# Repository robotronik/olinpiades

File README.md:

# Git pour les yeux du char des ol'INPiade

## Installation du dépot :
Pour cloner ce dépot:
```
git clone --recurse-submodules git@github.com:robotronik/olinpiades.git
```
## pré-requis : 
 
### Programmation
- arm-none-eabi-gcc: pour compiler le programme du stm32 ainsi que ces librairies (arm-none-eabi-**** sur arch linux)
- openocd: pour envoyer le programme au stm32
- meson pour compiler
### Génération des images
- Python
### Carte élctronique : 
- kicad 5

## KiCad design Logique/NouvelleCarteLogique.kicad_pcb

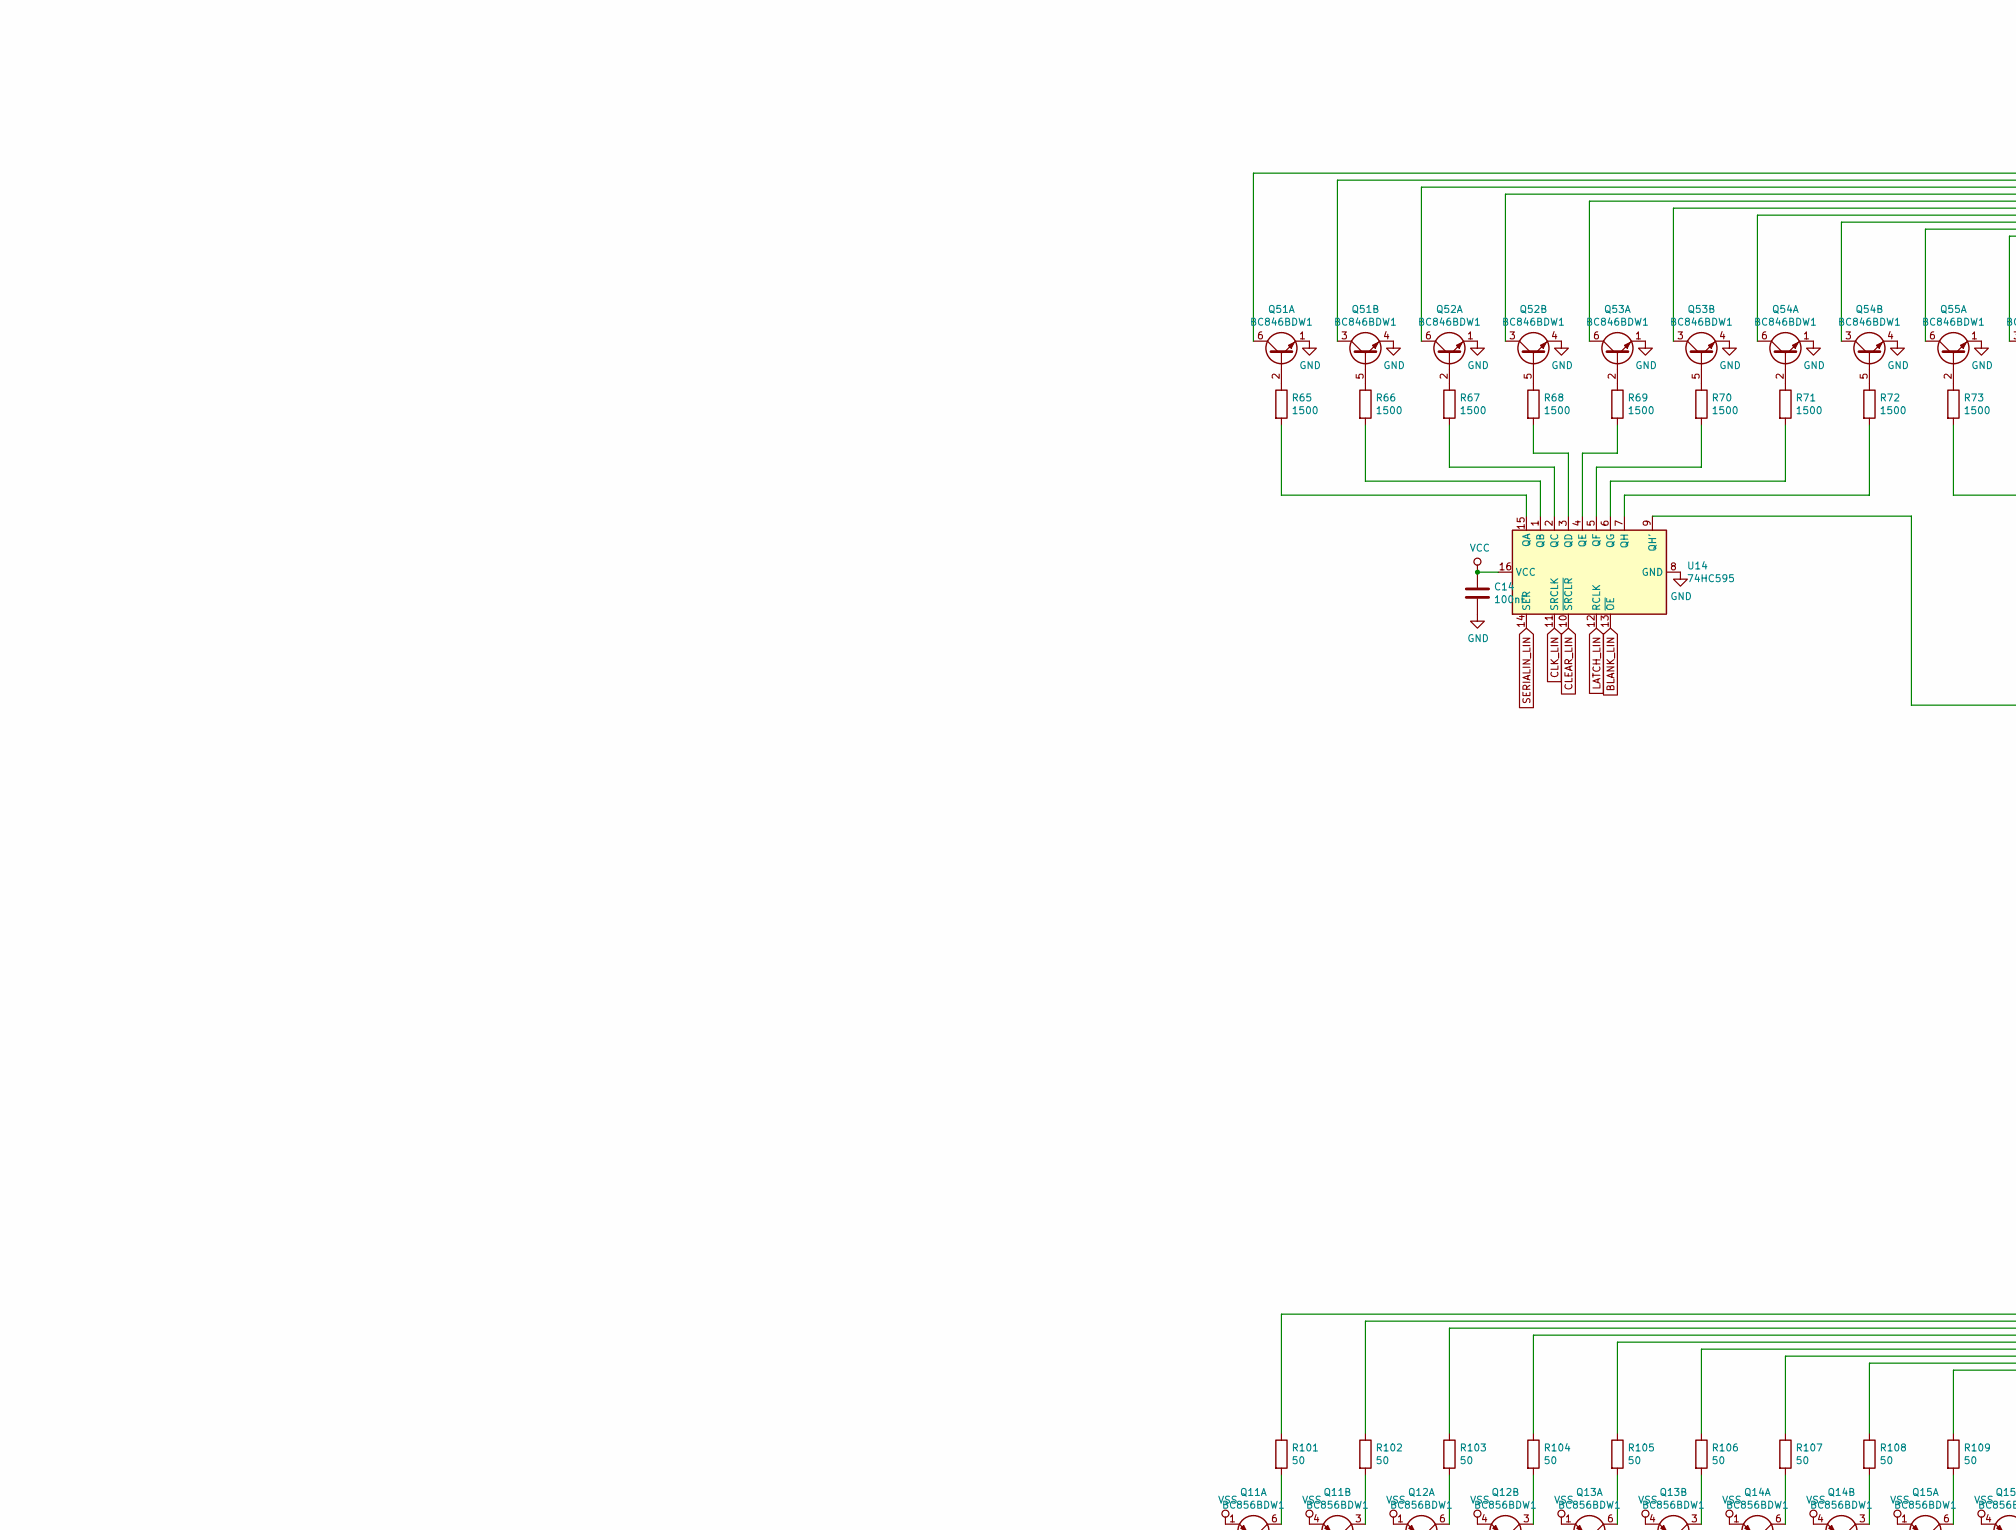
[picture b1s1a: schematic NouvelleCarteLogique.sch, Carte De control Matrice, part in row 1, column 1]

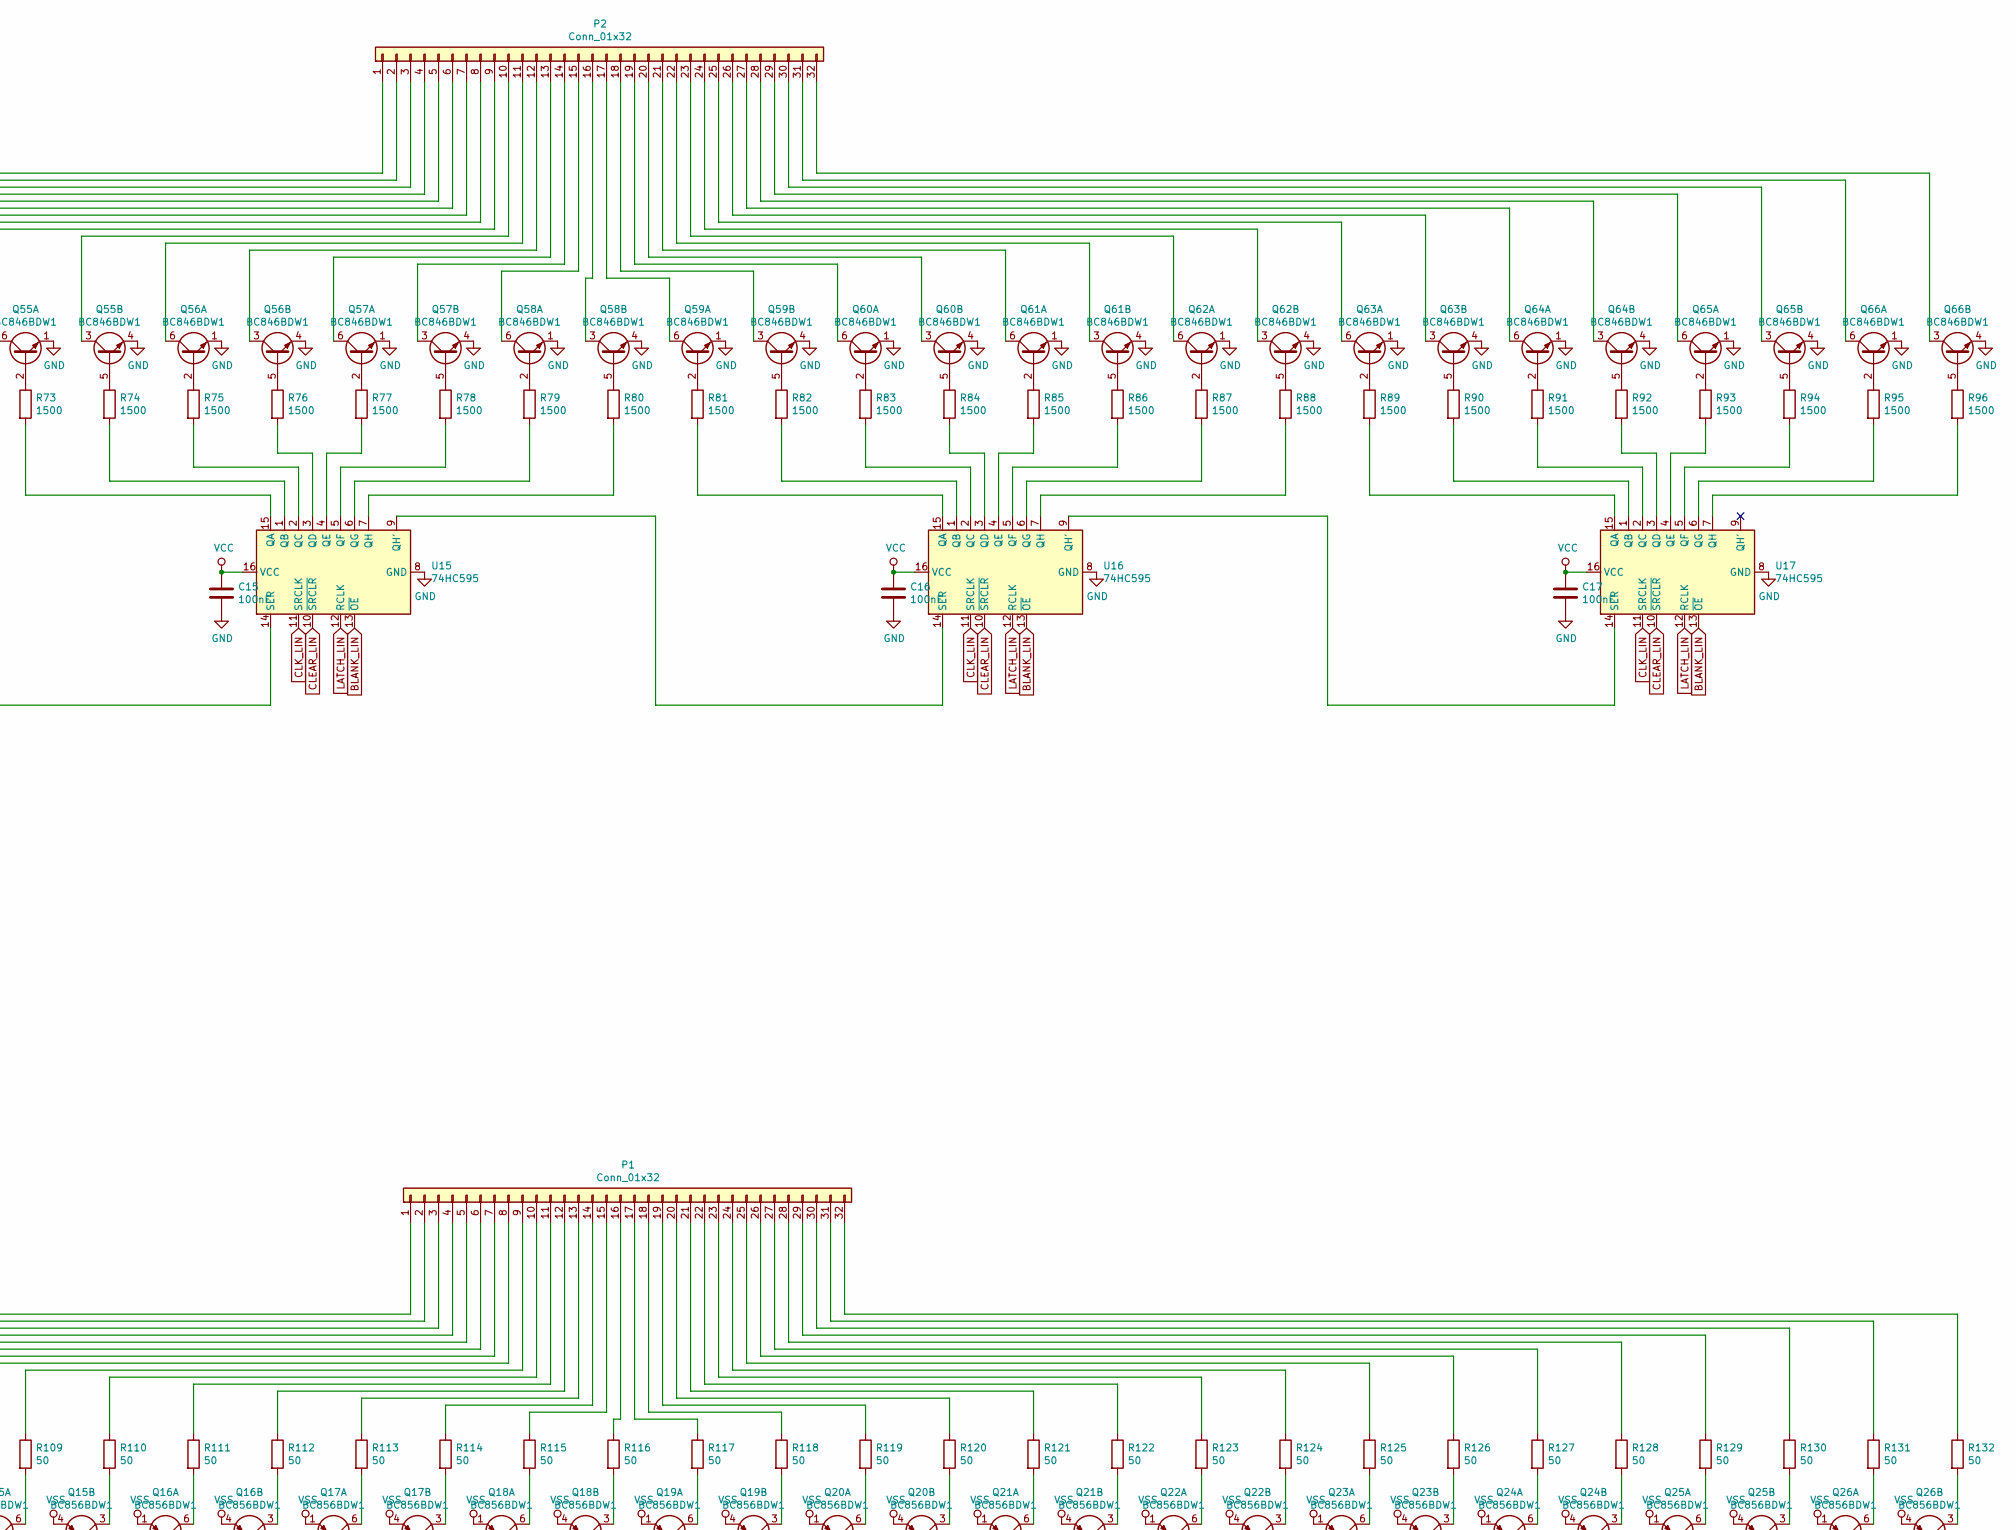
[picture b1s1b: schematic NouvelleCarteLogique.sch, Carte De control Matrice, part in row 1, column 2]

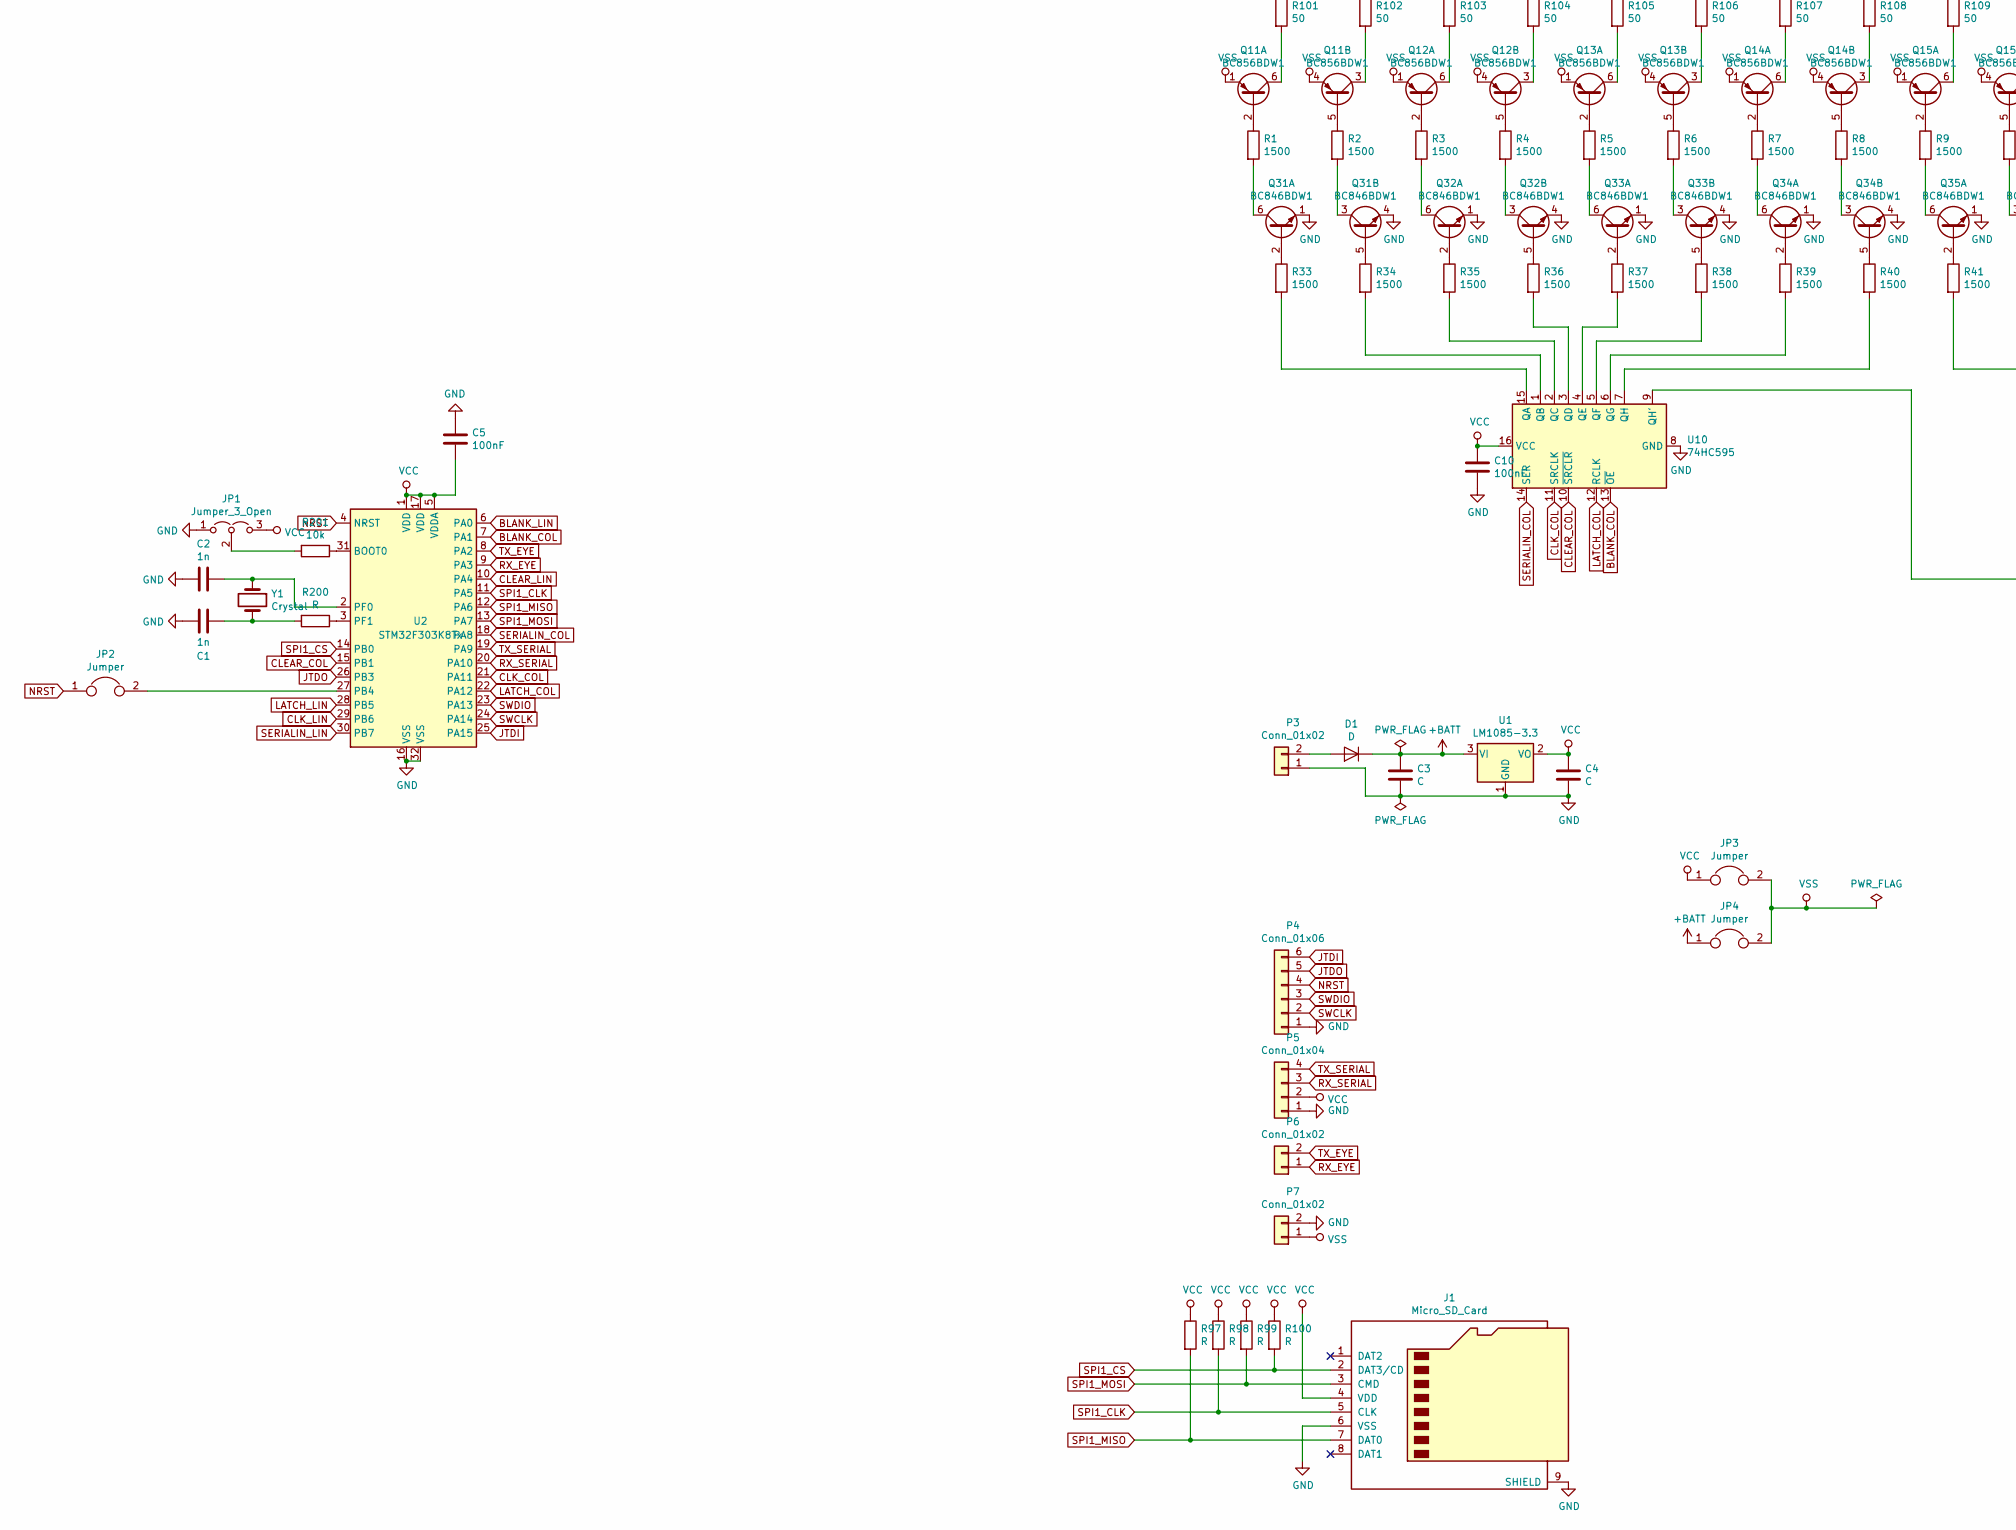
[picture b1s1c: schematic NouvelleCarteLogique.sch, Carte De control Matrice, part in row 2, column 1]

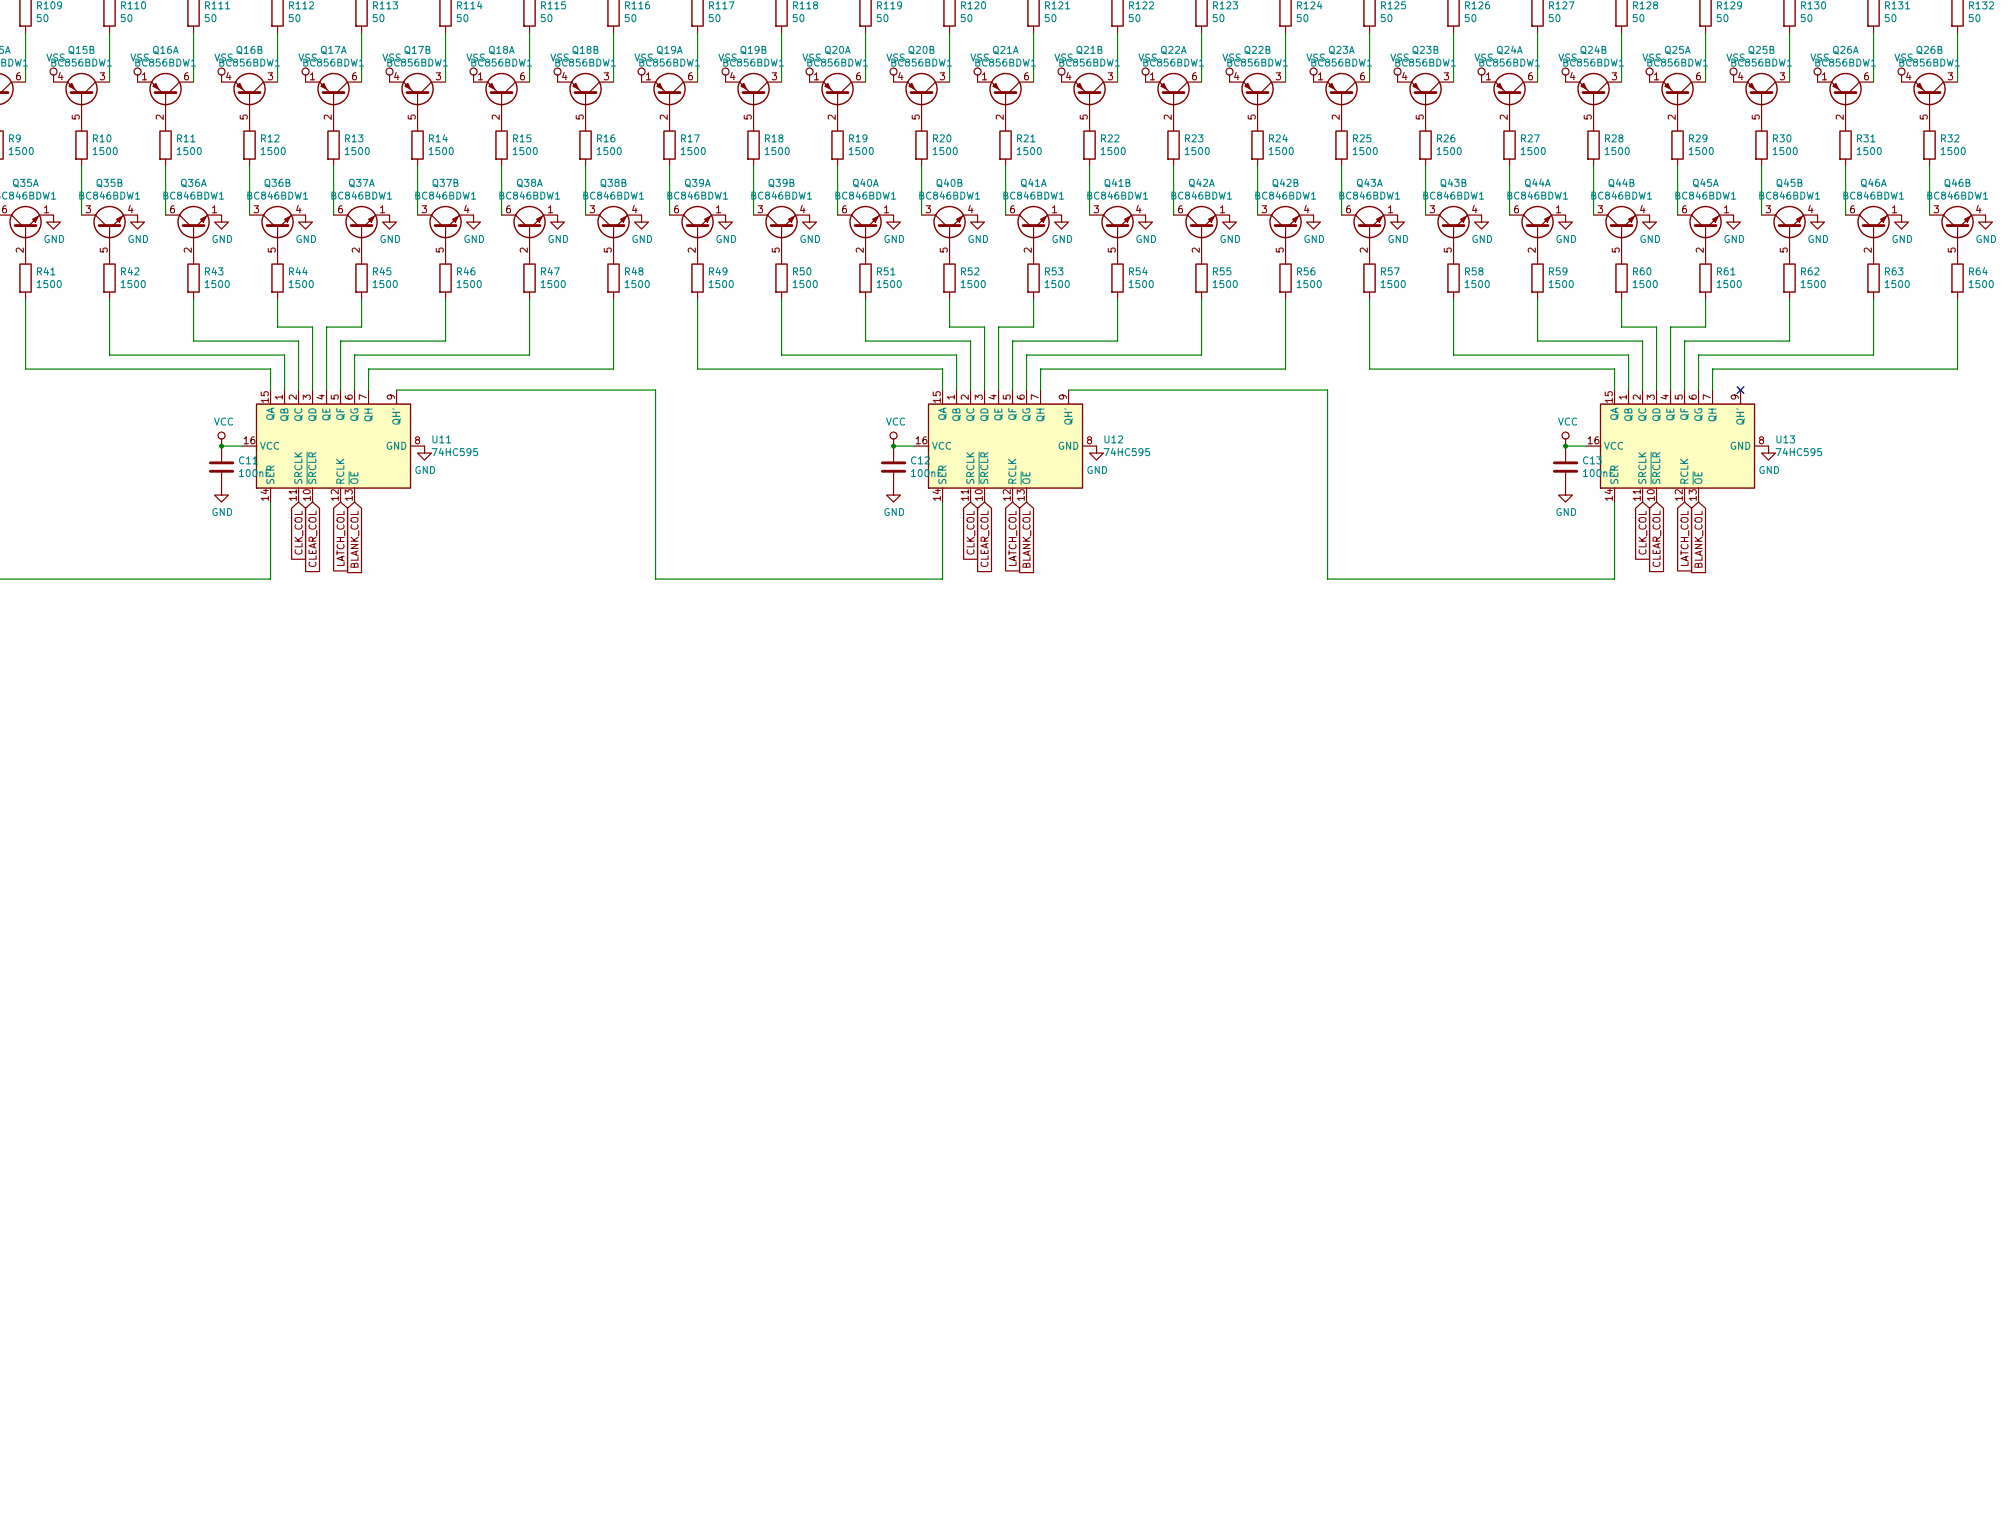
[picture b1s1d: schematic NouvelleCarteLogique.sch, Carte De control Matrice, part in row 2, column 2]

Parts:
C1, C2: 1n; C_0805_2012Metric_Pad1.15x1.40mm_HandSolder
C3, C4: C; C_0805_2012Metric_Pad1.15x1.40mm_HandSolder
C5, C10, C11, C12, C13, C14, C15, C16, C17: 100nF; C_0805_2012Metric_Pad1.15x1.40mm_HandSolder
D1: D; D_SMA_Handsoldering
J1: Micro_SD_Card; microSD_HC_Wuerth_693072010801
JP1: Jumper_3_Open; PinHeader_1x03_P2.54mm_Vertical
JP2, JP3, JP4: Jumper; R_0805_2012Metric_Pad1.15x1.40mm_HandSolder
P1, P2: Conn_01x32; PinHeader_1x32_P2.54mm_Vertical
P3, P6, P7: Conn_01x02; TerminalBlock_bornier-2_P5.08mm
P4: Conn_01x06; PinHeader_1x06_P2.54mm_Horizontal
P5: Conn_01x04; PinHeader_1x04_P2.54mm_Horizontal
Q11, Q12, Q13, Q14, Q15, Q16, Q17, Q18, Q19, Q20, Q21, Q22, Q23, Q24, Q25, Q26: BC856BDW1; SOT-363_SC-70-6
Q31, Q32, Q33, Q34, Q35, Q36, Q37, Q38, Q39, Q40, Q41, Q42, Q43, Q44, Q45, Q46, Q51, Q52, Q53, Q54, Q55, Q56, Q57, Q58, Q59, Q60, Q61, Q62, Q63, Q64, Q65, Q66: BC846BDW1; SOT-363_SC-70-6
R1, R2, R3, R4, R5, R6, R7, R8, R9, R10, R11, R12, R13, R14, R15, R16, R17, R18, R19, R20, R21, R22, R23, R24, R25, R26, R27, R28, R29, R30, R31, R32, R33, R34, R35, R36, R37, R38, R39, R40, R41, R42, R43, R44, R45, R46, R47, R48, R49, R50, R51, R52, R53, R54, R55, R56, R57, R58, R59, R60, R61, R62, R63, R64, R65, R66, R67, R68, R69, R70, R71, R72, R73, R74, R75, R76, R77, R78, R79, R80, R81, R82, R83, R84, R85, R86, R87, R88, R89, R90, R91, R92, R93, R94, R95, R96: 1500; R_0805_2012Metric_Pad1.15x1.40mm_HandSolder
R97, R98, R99, R100, R200: R; R_0805_2012Metric_Pad1.15x1.40mm_HandSolder
R101, R102, R103, R104, R105, R106, R107, R108, R109, R110, R111, R112, R113, R114, R115, R116, R117, R118, R119, R120, R121, R122, R123, R124, R125, R126, R127, R128, R129, R130, R131, R132: 50; R_0805_2012Metric_Pad1.15x1.40mm_HandSolder
R201: 10k; R_0805_2012Metric_Pad1.15x1.40mm_HandSolder
U1: LM1085-3.3; TO-263-3_TabPin2
U2: STM32F303K8Tx; LQFP-32_7x7mm_P0.8mm
U10, U11, U12, U13, U14, U15, U16, U17: 74HC595; TSSOP-16_4.4x5mm_P0.65mm
Y1: Crystal; Crystal_HC49-4H_Vertical

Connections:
+BATT: C3.1, D1.1 (K), JP4.1, U1.3 (VI)
BLANK_COL: U2.7 (PA1), U10.13 (~OE), U11.13 (~OE), U12.13 (~OE), U13.13 (~OE)
BLANK_LIN: U2.6 (PA0), U14.13 (~OE), U15.13 (~OE), U16.13 (~OE), U17.13 (~OE)
CLEAR_COL: U2.15 (PB1), U10.10 (~SRCLR), U11.10 (~SRCLR), U12.10 (~SRCLR), U13.10 (~SRCLR)
CLEAR_LIN: U2.10 (PA4), U14.10 (~SRCLR), U15.10 (~SRCLR), U16.10 (~SRCLR), U17.10 (~SRCLR)
CLK_COL: U2.21 (PA11), U10.11 (SRCLK), U11.11 (SRCLK), U12.11 (SRCLK), U13.11 (SRCLK)
CLK_LIN: U2.29 (PB6), U14.11 (SRCLK), U15.11 (SRCLK), U16.11 (SRCLK), U17.11 (SRCLK)
GND: C1.2, C2.2, C3.2, C4.2, C5.1, C10.2, C11.2, C12.2, C13.2, C14.2, C15.2, C16.2, C17.2, J1.6 (VSS), J1.9 (SHIELD), JP1.1 (A), P3.1, P4.1, P5.1, P7.2, Q31.1 (E1), Q31.4 (E2), Q32.1 (E1), Q32.4 (E2), Q33.1 (E1), Q33.4 (E2), Q34.1 (E1), Q34.4 (E2), Q35.1 (E1), Q35.4 (E2), Q36.1 (E1), Q36.4 (E2), Q37.1 (E1), Q37.4 (E2), Q38.1 (E1), Q38.4 (E2), Q39.1 (E1), Q39.4 (E2), Q40.1 (E1), Q40.4 (E2), Q41.1 (E1), Q41.4 (E2), Q42.1 (E1), Q42.4 (E2), Q43.1 (E1), Q43.4 (E2), Q44.1 (E1), Q44.4 (E2), Q45.1 (E1), Q45.4 (E2), Q46.1 (E1), Q46.4 (E2), Q51.1 (E1), Q51.4 (E2), Q52.1 (E1), Q52.4 (E2), Q53.1 (E1), Q53.4 (E2), Q54.1 (E1), Q54.4 (E2), Q55.1 (E1), Q55.4 (E2), Q56.1 (E1), Q56.4 (E2), Q57.1 (E1), Q57.4 (E2), Q58.1 (E1), Q58.4 (E2), Q59.1 (E1), Q59.4 (E2), Q60.1 (E1), Q60.4 (E2), Q61.1 (E1), Q61.4 (E2), Q62.1 (E1), Q62.4 (E2), Q63.1 (E1), Q63.4 (E2), Q64.1 (E1), Q64.4 (E2), Q65.1 (E1), Q65.4 (E2), Q66.1 (E1), Q66.4 (E2), U1.1 (GND), U2.16 (VSS), U2.32 (VSS), U10.8 (GND), U11.8 (GND), U12.8 (GND), U13.8 (GND), U14.8 (GND), U15.8 (GND), U16.8 (GND), U17.8 (GND)
JTDI: P4.6, U2.25 (PA15)
JTDO: P4.5, U2.26 (PB3)
LATCH_COL: U2.22 (PA12), U10.12 (RCLK), U11.12 (RCLK), U12.12 (RCLK), U13.12 (RCLK)
LATCH_LIN: U2.28 (PB5), U14.12 (RCLK), U15.12 (RCLK), U16.12 (RCLK), U17.12 (RCLK)
NRST: JP2.1, P4.4, U2.4 (NRST)
unnamed: C1.1, R200.2, Y1.2
unnamed: C2.1, U2.2 (PF0), Y1.1
unnamed: D1.2 (A), P3.2
unnamed: JP1.2 (C), R201.2
unnamed: JP2.2, U2.27 (PB4)
unnamed: P1.1, R101.1
unnamed: P1.2, R102.1
unnamed: P1.3, R103.1
unnamed: P1.4, R104.1
unnamed: P1.5, R105.1
unnamed: P1.6, R106.1
unnamed: P1.7, R107.1
unnamed: P1.8, R108.1
unnamed: P1.9, R109.1
unnamed: P1.10, R110.1
unnamed: P1.11, R111.1
unnamed: P1.12, R112.1
unnamed: P1.13, R113.1
unnamed: P1.14, R114.1
unnamed: P1.15, R115.1
unnamed: P1.16, R116.1
unnamed: P1.17, R117.1
unnamed: P1.18, R118.1
unnamed: P1.19, R119.1
unnamed: P1.20, R120.1
unnamed: P1.21, R121.1
unnamed: P1.22, R122.1
unnamed: P1.23, R123.1
unnamed: P1.24, R124.1
unnamed: P1.25, R125.1
unnamed: P1.26, R126.1
unnamed: P1.27, R127.1
unnamed: P1.28, R128.1
unnamed: P1.29, R129.1
unnamed: P1.30, R130.1
unnamed: P1.31, R131.1
unnamed: P1.32, R132.1
unnamed: P2.1, Q51.6 (C1)
unnamed: P2.2, Q51.3 (C2)
unnamed: P2.3, Q52.6 (C1)
unnamed: P2.4, Q52.3 (C2)
unnamed: P2.5, Q53.6 (C1)
unnamed: P2.6, Q53.3 (C2)
unnamed: P2.7, Q54.6 (C1)
unnamed: P2.8, Q54.3 (C2)
unnamed: P2.9, Q55.6 (C1)
unnamed: P2.10, Q55.3 (C2)
unnamed: P2.11, Q56.6 (C1)
unnamed: P2.12, Q56.3 (C2)
unnamed: P2.13, Q57.6 (C1)
unnamed: P2.14, Q57.3 (C2)
unnamed: P2.15, Q58.6 (C1)
unnamed: P2.16, Q58.3 (C2)
unnamed: P2.17, Q59.6 (C1)
unnamed: P2.18, Q59.3 (C2)
unnamed: P2.19, Q60.6 (C1)
unnamed: P2.20, Q60.3 (C2)
unnamed: P2.21, Q61.6 (C1)
unnamed: P2.22, Q61.3 (C2)
unnamed: P2.23, Q62.6 (C1)
unnamed: P2.24, Q62.3 (C2)
unnamed: P2.25, Q63.6 (C1)
unnamed: P2.26, Q63.3 (C2)
unnamed: P2.27, Q64.6 (C1)
unnamed: P2.28, Q64.3 (C2)
unnamed: P2.29, Q65.6 (C1)
unnamed: P2.30, Q65.3 (C2)
unnamed: P2.31, Q66.6 (C1)
unnamed: P2.32, Q66.3 (C2)
unnamed: Q11.2 (B1), R1.1
unnamed: Q11.3 (C2), R102.2
unnamed: Q11.5 (B2), R2.1
unnamed: Q11.6 (C1), R101.2
unnamed: Q12.2 (B1), R3.1
unnamed: Q12.3 (C2), R104.2
unnamed: Q12.5 (B2), R4.1
unnamed: Q12.6 (C1), R103.2
unnamed: Q13.2 (B1), R5.1
unnamed: Q13.3 (C2), R106.2
unnamed: Q13.5 (B2), R6.1
unnamed: Q13.6 (C1), R105.2
unnamed: Q14.2 (B1), R7.1
unnamed: Q14.3 (C2), R108.2
unnamed: Q14.5 (B2), R8.1
unnamed: Q14.6 (C1), R107.2
unnamed: Q15.2 (B1), R9.1
unnamed: Q15.3 (C2), R110.2
unnamed: Q15.5 (B2), R10.1
unnamed: Q15.6 (C1), R109.2
unnamed: Q16.2 (B1), R11.1
unnamed: Q16.3 (C2), R112.2
unnamed: Q16.5 (B2), R12.1
unnamed: Q16.6 (C1), R111.2
unnamed: Q17.2 (B1), R13.1
unnamed: Q17.3 (C2), R114.2
unnamed: Q17.5 (B2), R14.1
unnamed: Q17.6 (C1), R113.2
unnamed: Q18.2 (B1), R15.1
unnamed: Q18.3 (C2), R116.2
unnamed: Q18.5 (B2), R16.1
unnamed: Q18.6 (C1), R115.2
unnamed: Q19.2 (B1), R17.1
unnamed: Q19.3 (C2), R118.2
unnamed: Q19.5 (B2), R18.1
unnamed: Q19.6 (C1), R117.2
unnamed: Q20.2 (B1), R19.1
unnamed: Q20.3 (C2), R120.2
unnamed: Q20.5 (B2), R20.1
unnamed: Q20.6 (C1), R119.2
unnamed: Q21.2 (B1), R21.1
unnamed: Q21.3 (C2), R122.2
unnamed: Q21.5 (B2), R22.1
unnamed: Q21.6 (C1), R121.2
unnamed: Q22.2 (B1), R23.1
unnamed: Q22.3 (C2), R124.2
unnamed: Q22.5 (B2), R24.1
unnamed: Q22.6 (C1), R123.2
unnamed: Q23.2 (B1), R25.1
unnamed: Q23.3 (C2), R126.2
unnamed: Q23.5 (B2), R26.1
unnamed: Q23.6 (C1), R125.2
unnamed: Q24.2 (B1), R27.1
unnamed: Q24.3 (C2), R128.2
unnamed: Q24.5 (B2), R28.1
unnamed: Q24.6 (C1), R127.2
unnamed: Q25.2 (B1), R29.1
unnamed: Q25.3 (C2), R130.2
unnamed: Q25.5 (B2), R30.1
unnamed: Q25.6 (C1), R129.2
unnamed: Q26.2 (B1), R31.1
unnamed: Q26.3 (C2), R132.2
unnamed: Q26.5 (B2), R32.1
unnamed: Q26.6 (C1), R131.2
unnamed: Q31.2 (B1), R33.1
unnamed: Q31.3 (C2), R2.2
unnamed: Q31.5 (B2), R34.1
unnamed: Q31.6 (C1), R1.2
unnamed: Q32.2 (B1), R35.1
unnamed: Q32.3 (C2), R4.2
unnamed: Q32.5 (B2), R36.1
unnamed: Q32.6 (C1), R3.2
unnamed: Q33.2 (B1), R37.1
unnamed: Q33.3 (C2), R6.2
unnamed: Q33.5 (B2), R38.1
unnamed: Q33.6 (C1), R5.2
unnamed: Q34.2 (B1), R39.1
unnamed: Q34.3 (C2), R8.2
unnamed: Q34.5 (B2), R40.1
unnamed: Q34.6 (C1), R7.2
unnamed: Q35.2 (B1), R41.1
unnamed: Q35.3 (C2), R10.2
unnamed: Q35.5 (B2), R42.1
unnamed: Q35.6 (C1), R9.2
unnamed: Q36.2 (B1), R43.1
unnamed: Q36.3 (C2), R12.2
unnamed: Q36.5 (B2), R44.1
unnamed: Q36.6 (C1), R11.2
unnamed: Q37.2 (B1), R45.1
unnamed: Q37.3 (C2), R14.2
unnamed: Q37.5 (B2), R46.1
unnamed: Q37.6 (C1), R13.2
unnamed: Q38.2 (B1), R47.1
unnamed: Q38.3 (C2), R16.2
unnamed: Q38.5 (B2), R48.1
unnamed: Q38.6 (C1), R15.2
unnamed: Q39.2 (B1), R49.1
unnamed: Q39.3 (C2), R18.2
unnamed: Q39.5 (B2), R50.1
unnamed: Q39.6 (C1), R17.2
unnamed: Q40.2 (B1), R51.1
unnamed: Q40.3 (C2), R20.2
unnamed: Q40.5 (B2), R52.1
unnamed: Q40.6 (C1), R19.2
unnamed: Q41.2 (B1), R53.1
unnamed: Q41.3 (C2), R22.2
unnamed: Q41.5 (B2), R54.1
unnamed: Q41.6 (C1), R21.2
unnamed: Q42.2 (B1), R55.1
unnamed: Q42.3 (C2), R24.2
unnamed: Q42.5 (B2), R56.1
unnamed: Q42.6 (C1), R23.2
unnamed: Q43.2 (B1), R57.1
unnamed: Q43.3 (C2), R26.2
unnamed: Q43.5 (B2), R58.1
unnamed: Q43.6 (C1), R25.2
unnamed: Q44.2 (B1), R59.1
unnamed: Q44.3 (C2), R28.2
unnamed: Q44.5 (B2), R60.1
unnamed: Q44.6 (C1), R27.2
unnamed: Q45.2 (B1), R61.1
unnamed: Q45.3 (C2), R30.2
unnamed: Q45.5 (B2), R62.1
unnamed: Q45.6 (C1), R29.2
unnamed: Q46.2 (B1), R63.1
unnamed: Q46.3 (C2), R32.2
unnamed: Q46.5 (B2), R64.1
unnamed: Q46.6 (C1), R31.2
unnamed: Q51.2 (B1), R65.1
unnamed: Q51.5 (B2), R66.1
unnamed: Q52.2 (B1), R67.1
unnamed: Q52.5 (B2), R68.1
unnamed: Q53.2 (B1), R69.1
unnamed: Q53.5 (B2), R70.1
unnamed: Q54.2 (B1), R71.1
unnamed: Q54.5 (B2), R72.1
unnamed: Q55.2 (B1), R73.1
unnamed: Q55.5 (B2), R74.1
unnamed: Q56.2 (B1), R75.1
unnamed: Q56.5 (B2), R76.1
unnamed: Q57.2 (B1), R77.1
unnamed: Q57.5 (B2), R78.1
unnamed: Q58.2 (B1), R79.1
unnamed: Q58.5 (B2), R80.1
unnamed: Q59.2 (B1), R81.1
unnamed: Q59.5 (B2), R82.1
unnamed: Q60.2 (B1), R83.1
unnamed: Q60.5 (B2), R84.1
unnamed: Q61.2 (B1), R85.1
unnamed: Q61.5 (B2), R86.1
unnamed: Q62.2 (B1), R87.1
unnamed: Q62.5 (B2), R88.1
unnamed: Q63.2 (B1), R89.1
unnamed: Q63.5 (B2), R90.1
unnamed: Q64.2 (B1), R91.1
unnamed: Q64.5 (B2), R92.1
unnamed: Q65.2 (B1), R93.1
unnamed: Q65.5 (B2), R94.1
unnamed: Q66.2 (B1), R95.1
unnamed: Q66.5 (B2), R96.1
unnamed: R33.2, U10.15 (QA)
unnamed: R34.2, U10.1 (QB)
unnamed: R35.2, U10.2 (QC)
unnamed: R36.2, U10.3 (QD)
unnamed: R37.2, U10.4 (QE)
unnamed: R38.2, U10.5 (QF)
unnamed: R39.2, U10.6 (QG)
unnamed: R40.2, U10.7 (QH)
unnamed: R41.2, U11.15 (QA)
unnamed: R42.2, U11.1 (QB)
unnamed: R43.2, U11.2 (QC)
unnamed: R44.2, U11.3 (QD)
unnamed: R45.2, U11.4 (QE)
unnamed: R46.2, U11.5 (QF)
unnamed: R47.2, U11.6 (QG)
unnamed: R48.2, U11.7 (QH)
unnamed: R49.2, U12.15 (QA)
unnamed: R50.2, U12.1 (QB)
unnamed: R51.2, U12.2 (QC)
unnamed: R52.2, U12.3 (QD)
unnamed: R53.2, U12.4 (QE)
unnamed: R54.2, U12.5 (QF)
unnamed: R55.2, U12.6 (QG)
unnamed: R56.2, U12.7 (QH)
unnamed: R57.2, U13.15 (QA)
unnamed: R58.2, U13.1 (QB)
unnamed: R59.2, U13.2 (QC)
unnamed: R60.2, U13.3 (QD)
unnamed: R61.2, U13.4 (QE)
unnamed: R62.2, U13.5 (QF)
unnamed: R63.2, U13.6 (QG)
unnamed: R64.2, U13.7 (QH)
unnamed: R65.2, U14.15 (QA)
unnamed: R66.2, U14.1 (QB)
unnamed: R67.2, U14.2 (QC)
unnamed: R68.2, U14.3 (QD)
unnamed: R69.2, U14.4 (QE)
unnamed: R70.2, U14.5 (QF)
unnamed: R71.2, U14.6 (QG)
unnamed: R72.2, U14.7 (QH)
unnamed: R73.2, U15.15 (QA)
unnamed: R74.2, U15.1 (QB)
unnamed: R75.2, U15.2 (QC)
unnamed: R76.2, U15.3 (QD)
unnamed: R77.2, U15.4 (QE)
unnamed: R78.2, U15.5 (QF)
unnamed: R79.2, U15.6 (QG)
unnamed: R80.2, U15.7 (QH)
unnamed: R81.2, U16.15 (QA)
unnamed: R82.2, U16.1 (QB)
unnamed: R83.2, U16.2 (QC)
unnamed: R84.2, U16.3 (QD)
unnamed: R85.2, U16.4 (QE)
unnamed: R86.2, U16.5 (QF)
unnamed: R87.2, U16.6 (QG)
unnamed: R88.2, U16.7 (QH)
unnamed: R89.2, U17.15 (QA)
unnamed: R90.2, U17.1 (QB)
unnamed: R91.2, U17.2 (QC)
unnamed: R92.2, U17.3 (QD)
unnamed: R93.2, U17.4 (QE)
unnamed: R94.2, U17.5 (QF)
unnamed: R95.2, U17.6 (QG)
unnamed: R96.2, U17.7 (QH)
unnamed: R200.1, U2.3 (PF1)
unnamed: R201.1, U2.31 (BOOT0)
unnamed: U10.9 (QH'), U11.14 (SER)
unnamed: U11.9 (QH'), U12.14 (SER)
unnamed: U12.9 (QH'), U13.14 (SER)
unnamed: U14.9 (QH'), U15.14 (SER)
unnamed: U15.9 (QH'), U16.14 (SER)
unnamed: U16.9 (QH'), U17.14 (SER)
RX_EYE: P6.1, U2.9 (PA3)
RX_SERIAL: P5.3, U2.20 (PA10)
SERIALIN_COL: U2.18 (PA8), U10.14 (SER)
SERIALIN_LIN: U2.30 (PB7), U14.14 (SER)
SPI1_CLK: J1.5 (CLK), R98.2, U2.11 (PA5)
SPI1_CS: J1.2 (DAT3/CD), R100.2, U2.14 (PB0)
SPI1_MISO: J1.7 (DAT0), R97.2, U2.12 (PA6)
SPI1_MOSI: J1.3 (CMD), R99.2, U2.13 (PA7)
SWCLK: P4.2, U2.24 (PA14)
SWDIO: P4.3, U2.23 (PA13)
TX_EYE: P6.2, U2.8 (PA2)
TX_SERIAL: P5.4, U2.19 (PA9)
VCC: C4.1, C5.2, C10.1, C11.1, C12.1, C13.1, C14.1, C15.1, C16.1, C17.1, J1.4 (VDD), JP1.3 (B), JP3.1, P5.2, R97.1, R98.1, R99.1, R100.1, U1.2 (VO), U2.1 (VDD), U2.5 (VDDA), U2.17 (VDD), U10.16 (VCC), U11.16 (VCC), U12.16 (VCC), U13.16 (VCC), U14.16 (VCC), U15.16 (VCC), U16.16 (VCC), U17.16 (VCC)
VSS: JP3.2, JP4.2, P7.1, Q11.1 (E1), Q11.4 (E2), Q12.1 (E1), Q12.4 (E2), Q13.1 (E1), Q13.4 (E2), Q14.1 (E1), Q14.4 (E2), Q15.1 (E1), Q15.4 (E2), Q16.1 (E1), Q16.4 (E2), Q17.1 (E1), Q17.4 (E2), Q18.1 (E1), Q18.4 (E2), Q19.1 (E1), Q19.4 (E2), Q20.1 (E1), Q20.4 (E2), Q21.1 (E1), Q21.4 (E2), Q22.1 (E1), Q22.4 (E2), Q23.1 (E1), Q23.4 (E2), Q24.1 (E1), Q24.4 (E2), Q25.1 (E1), Q25.4 (E2), Q26.1 (E1), Q26.4 (E2)
